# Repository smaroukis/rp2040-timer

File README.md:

# 10k-Hour-Timer-RP2040

An Eval Board for an RP2040 mcu + seven segment LED display + TM1638 driver + peripherals. 

## Project Structure

- `kicad/` - KiCad schematic and PCB design files
- `firmware/` - Firmware source code
- `datasheets/` - Component datasheets and documentation

## Hardware

This project uses the RP2040 microcontroller with supporting circuitry for power management, display drivers, and user interface components.
Note the firmware can be tested using a Raspberry Pi Pico board (original/v1 not Pico 2). 

## Getting Started

TODO - will post build log in the future.

## License

MIT License with other license files attached as used. 

## Hardware Revisions

### 2026-03-22 v1
Tagged commit: <link here>

Thanks to PCBWay for providing a partial discount which I put towards two pre-assemblied. Note that resistors R20 and R22 were populated with 220Ohms instead of 200Ohms as specified in the BOM. However these are just MOFSET gate protection resistors.

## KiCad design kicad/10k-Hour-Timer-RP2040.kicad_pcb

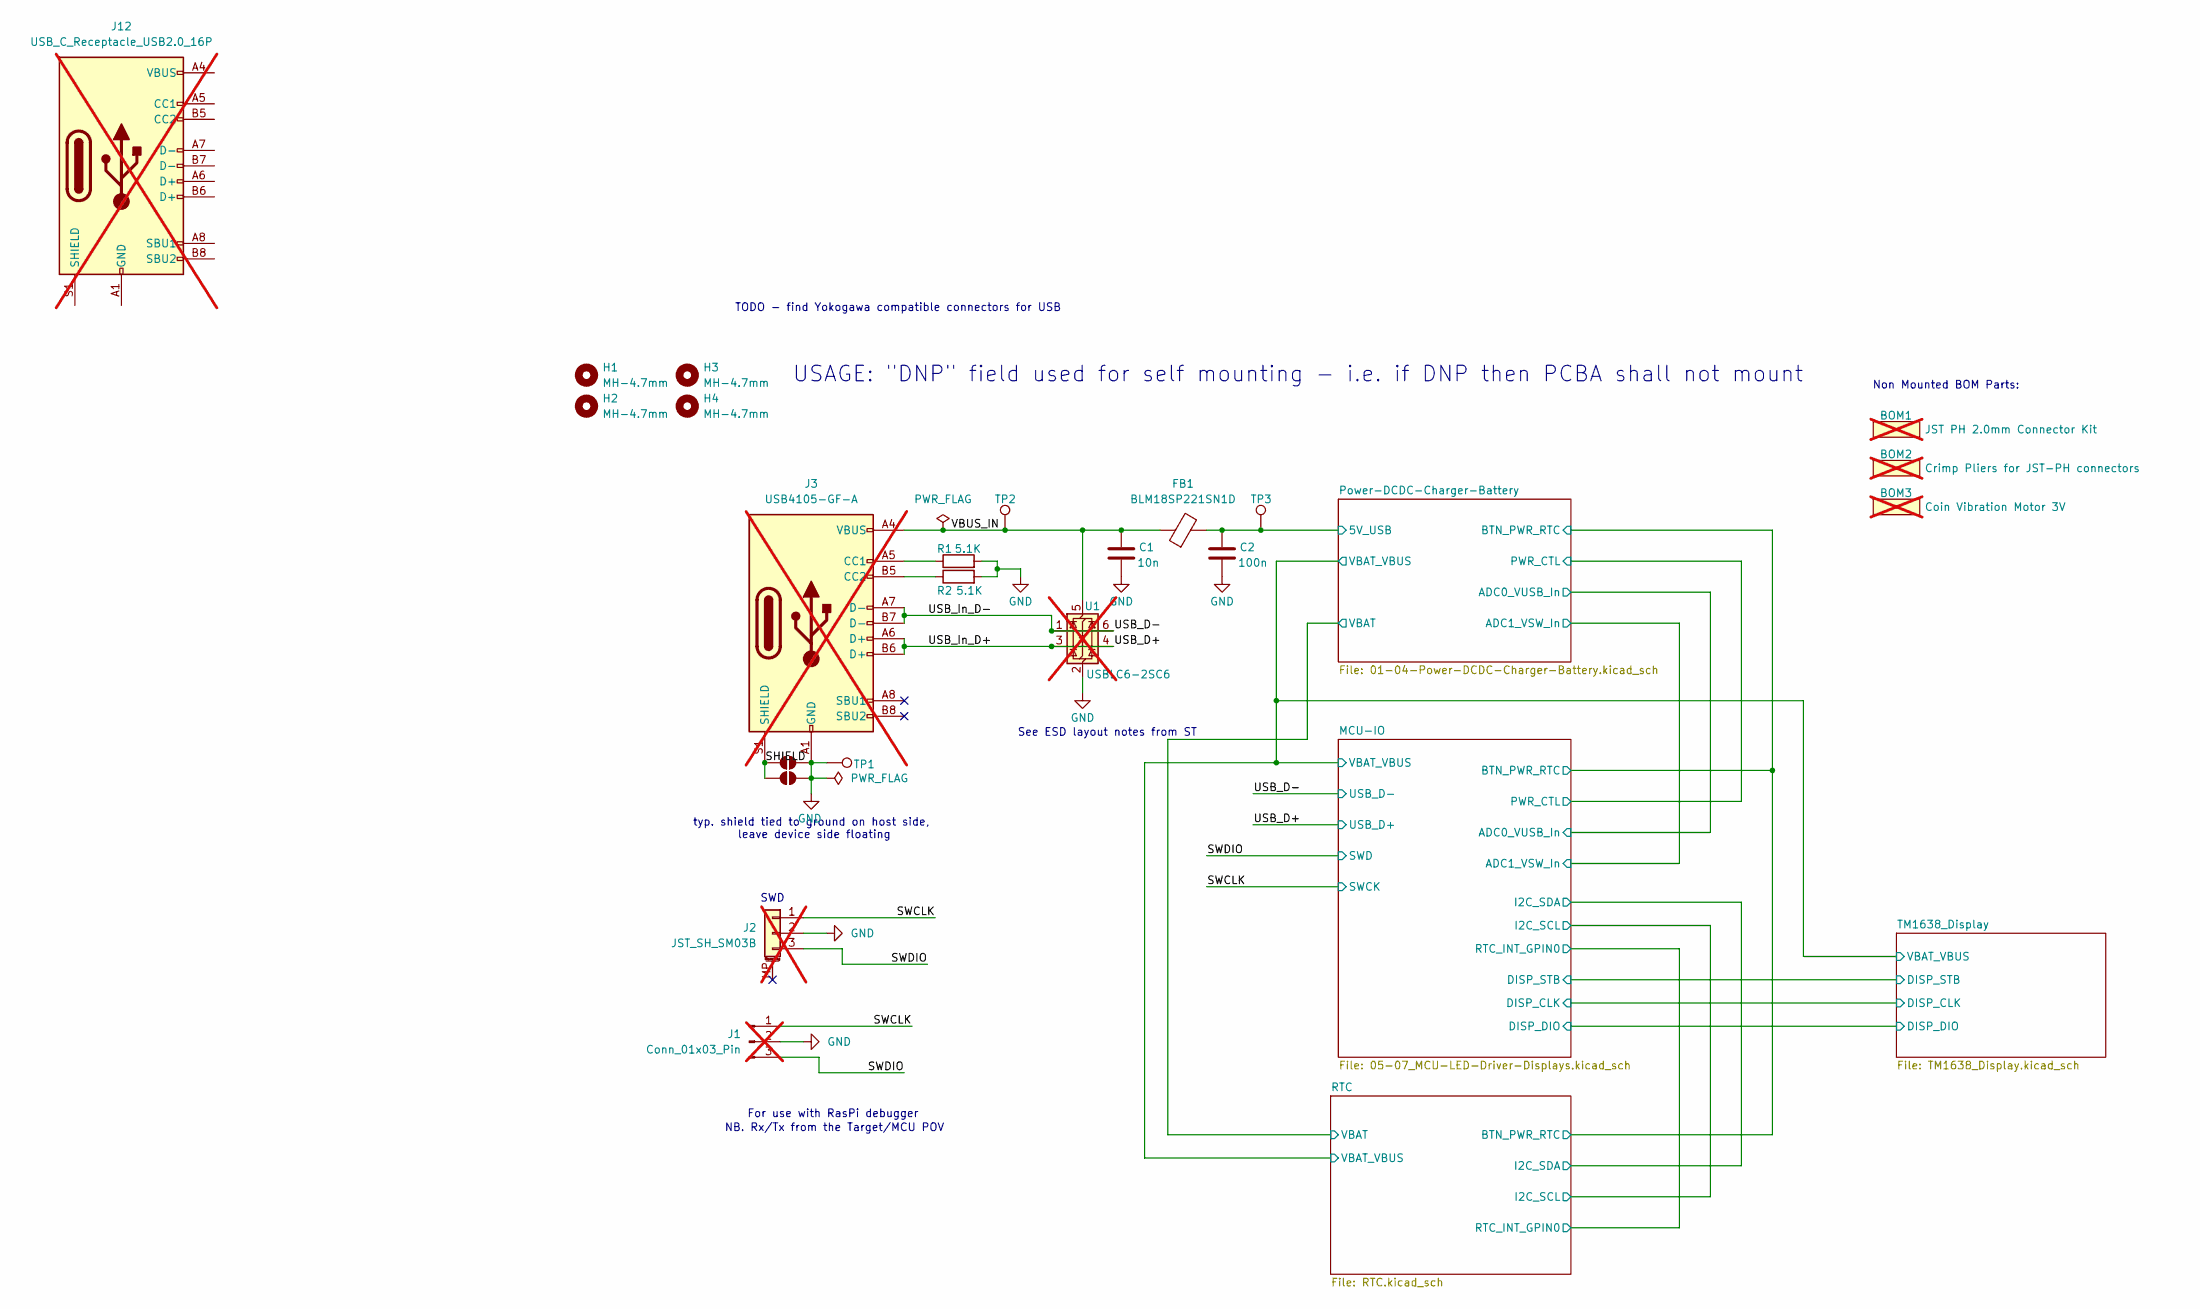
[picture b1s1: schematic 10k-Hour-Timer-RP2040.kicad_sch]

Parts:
BOM1: JST PH 2.0mm Connector Kit; not fitted
BOM2: Crimp Pliers for JST-PH connectors; MPN PA-09; not fitted
BOM3: Coin Vibration Motor 3V; MPN LCM0720A3134F; not fitted
C1: 10n; C_0603_1608Metric_Pad1.08x0.95mm_HandSolder; MPN (Generic)
C2: 100n; C_0603_1608Metric_Pad1.08x0.95mm_HandSolder; MPN (Generic)
FB1: BLM18SP221SN1D; BLM18SP221SN1D_BEADC1608X95N; MPN BLM18SP221SN1D
H1, H2, H3, H4: MH-4.7mm; MountingHole_4.7mm; MPN 8834
J1: Conn_01x03_Pin; PinHeader_1x03_P2.54mm_Vertical; MPN (Embedded); not fitted
J2: JST_SH_SM03B; JST_SH_SM03B-SRSS-TB_1x03-1MP_P1.00mm_Horizontal; MPN SM03B-SRSS-TB(LF)(SN); not fitted
J3: USB4105-GF-A; GCT_USB4105-GF-A; MPN USB4105-GF-A; not fitted
J12: USB_C_Receptacle_USB2.0_16P; USB_C_Receptacle_JAE_DX07S016JA1R1500; MPN DX07S016JA1R1500; not fitted
JP1, JP24: SolderJumper_2_Open; SolderJumper-2_P1.3mm_Open_RoundedPad1.0x1.5mm; MPN (Embedded)
R1, R2: 5.1K; R_0805_2012Metric_Pad1.20x1.40mm_HandSolder; MPN (Generic)
TP1: GND; TestPoint_THTPad_D2.0mm_Drill1.0mm; MPN (Embedded)
TP2: VBUS_IN; TestPoint_THTPad_D2.0mm_Drill1.0mm; MPN (Embedded)
TP3: VBUS; TestPoint_THTPad_D2.0mm_Drill1.0mm; MPN (Embedded)
U1: USBLC6-2SC6; SOT-23-6; MPN USBLC6-2SC6; not fitted

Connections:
/MCU-IO/ADC0_VUSB_In: C2.1, FB1.2, TP3.1; also elsewhere on the board
/SHIELD: J3.S1 (SHIELD), JP1.1 (A), JP24.1 (A)
/SWCLK: J1.1, J2.1; also elsewhere on the board
/SWDIO: J1.3, J2.3; also elsewhere on the board
/USB_D+: J3.A6 (D+), J3.B6 (D+), U1.3 (I/O2), U1.4 (I/O2); also elsewhere on the board
/USB_D-: J3.A7 (D-), J3.B7 (D-), U1.1 (I/O1), U1.6 (I/O1); also elsewhere on the board
/VBUS_IN: C1.1, FB1.1, J3.A4 (VBUS), J3.A9 (VBUS), J3.B4 (VBUS), J3.B9 (VBUS), TP2.1, U1.5 (VBUS)
GND: C1.2, C2.2, J1.2, J2.2, J3.A1 (GND), J3.A12 (GND), J3.B1 (GND), J3.B12 (GND), JP1.2 (B), JP24.2 (B), R1.2, R2.2, TP1.1, U1.2 (GND); also elsewhere on the board
unnamed: J3.A5 (CC1), R1.1
unnamed: J3.B5 (CC2), R2.1
unnamed: J12.A1 (GND), J12.A12 (GND), J12.B1 (GND), J12.B12 (GND)
unnamed: J12.A4 (VBUS), J12.A9 (VBUS), J12.B4 (VBUS), J12.B9 (VBUS)

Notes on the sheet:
For use with RasPi debugger
typ. shield tied to ground on host side, leave device side floating
See ESD layout notes from ST
Non Mounted BOM Parts:
TODO - find Yokogawa compatible connectors for USB
USAGE: "DNP" field used for self mounting - i.e. if DNP then PCBA shall not mount
SWD
NB. Rx/Tx from the Target/MCU POV

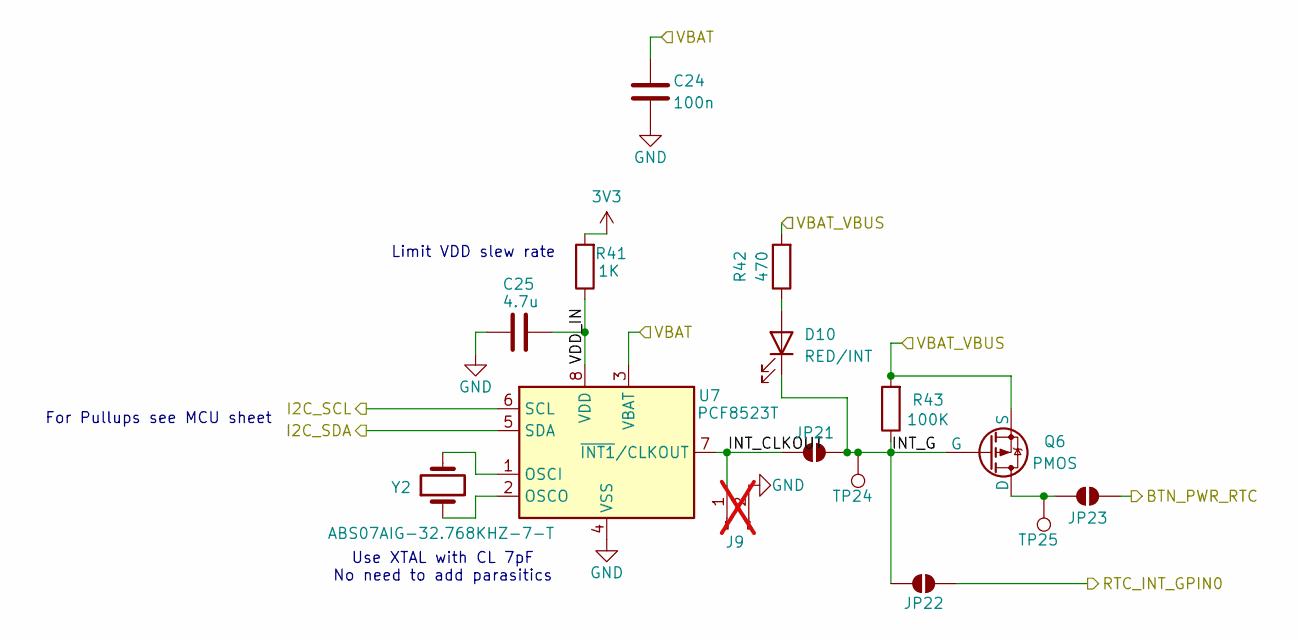
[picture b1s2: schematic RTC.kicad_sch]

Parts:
C24: 100n; C_0603_1608Metric_Pad1.08x0.95mm_HandSolder; MPN (Generic)
C25: 4.7u; C_0603_1608Metric_Pad1.08x0.95mm_HandSolder; MPN (Generic)
D10: RED/INT; LED_0805_2012Metric; MPN NCD0805R1
J9: Conn_01x02_Pin; PinHeader_1x02_P2.54mm_Vertical; not fitted
JP21, JP22, JP23: SolderJumper_2_Open; SolderJumper-2_P1.3mm_Open_RoundedPad1.0x1.5mm; MPN (Embedded)
Q6: PMOS; SOT-23; MPN SI2301CDS-T1-GE3
R41: 1K; R_0805_2012Metric_Pad1.20x1.40mm_HandSolder; MPN (Generic)
R42: 470; R_0805_2012Metric_Pad1.20x1.40mm_HandSolder; MPN (Generic)
R43: 100K; R_0805_2012Metric_Pad1.20x1.40mm_HandSolder; MPN (Generic)
TP24: INT_G; TestPoint_THTPad_D2.0mm_Drill1.0mm; MPN (Embedded)
TP25: INT_D; TestPoint_THTPad_D2.0mm_Drill1.0mm; MPN (Embedded)
U7: PCF8523T; SOIC-8_3.9x4.9mm_P1.27mm; MPN PCF8523T/1,118
Y2: ABS07AIG-32.768KHZ-7-T; Crystal_SMD_3215-2Pin_3.2x1.5mm; MPN ABS07AIG-32.768KHZ-7-T

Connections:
3V3: R41.2; also elsewhere on the board
/MCU-IO/I2C_SCL: U7.6 (SCL); also elsewhere on the board
/MCU-IO/I2C_SDA: U7.5 (SDA); also elsewhere on the board
/MCU-IO/IO_Gate: JP23.2 (B); also elsewhere on the board
/MCU-IO/RTC_INT_GPIN0: JP22.1 (A); also elsewhere on the board
/MCU-IO/VBAT_VBUS: Q6.3 (S), R42.2, R43.2; also elsewhere on the board
/Power-DCDC-Charger-Battery/VBAT: C24.1, U7.3 (VBAT); also elsewhere on the board
/RTC/INT_CLKOUT: J9.1, JP21.1 (A), U7.7 (~INT1/CLKOUT)
/RTC/INT_G: D10.1 (K), JP21.2 (B), JP22.2 (B), Q6.2 (G), R43.1, TP24.1
/RTC/VDD_IN: C25.1, R41.1, U7.8 (VDD)
GND: C24.2, C25.2, J9.2, U7.4 (VSS); also elsewhere on the board
unnamed: D10.2 (A), R42.1
unnamed: JP23.1 (A), Q6.1 (D), TP25.1
unnamed: U7.1 (OSCI), Y2.2
unnamed: U7.2 (OSCO), Y2.1

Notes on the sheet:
For Pullups see MCU sheet
Limit VDD slew rate
Use XTAL with CL 7pF No need to add parasitics

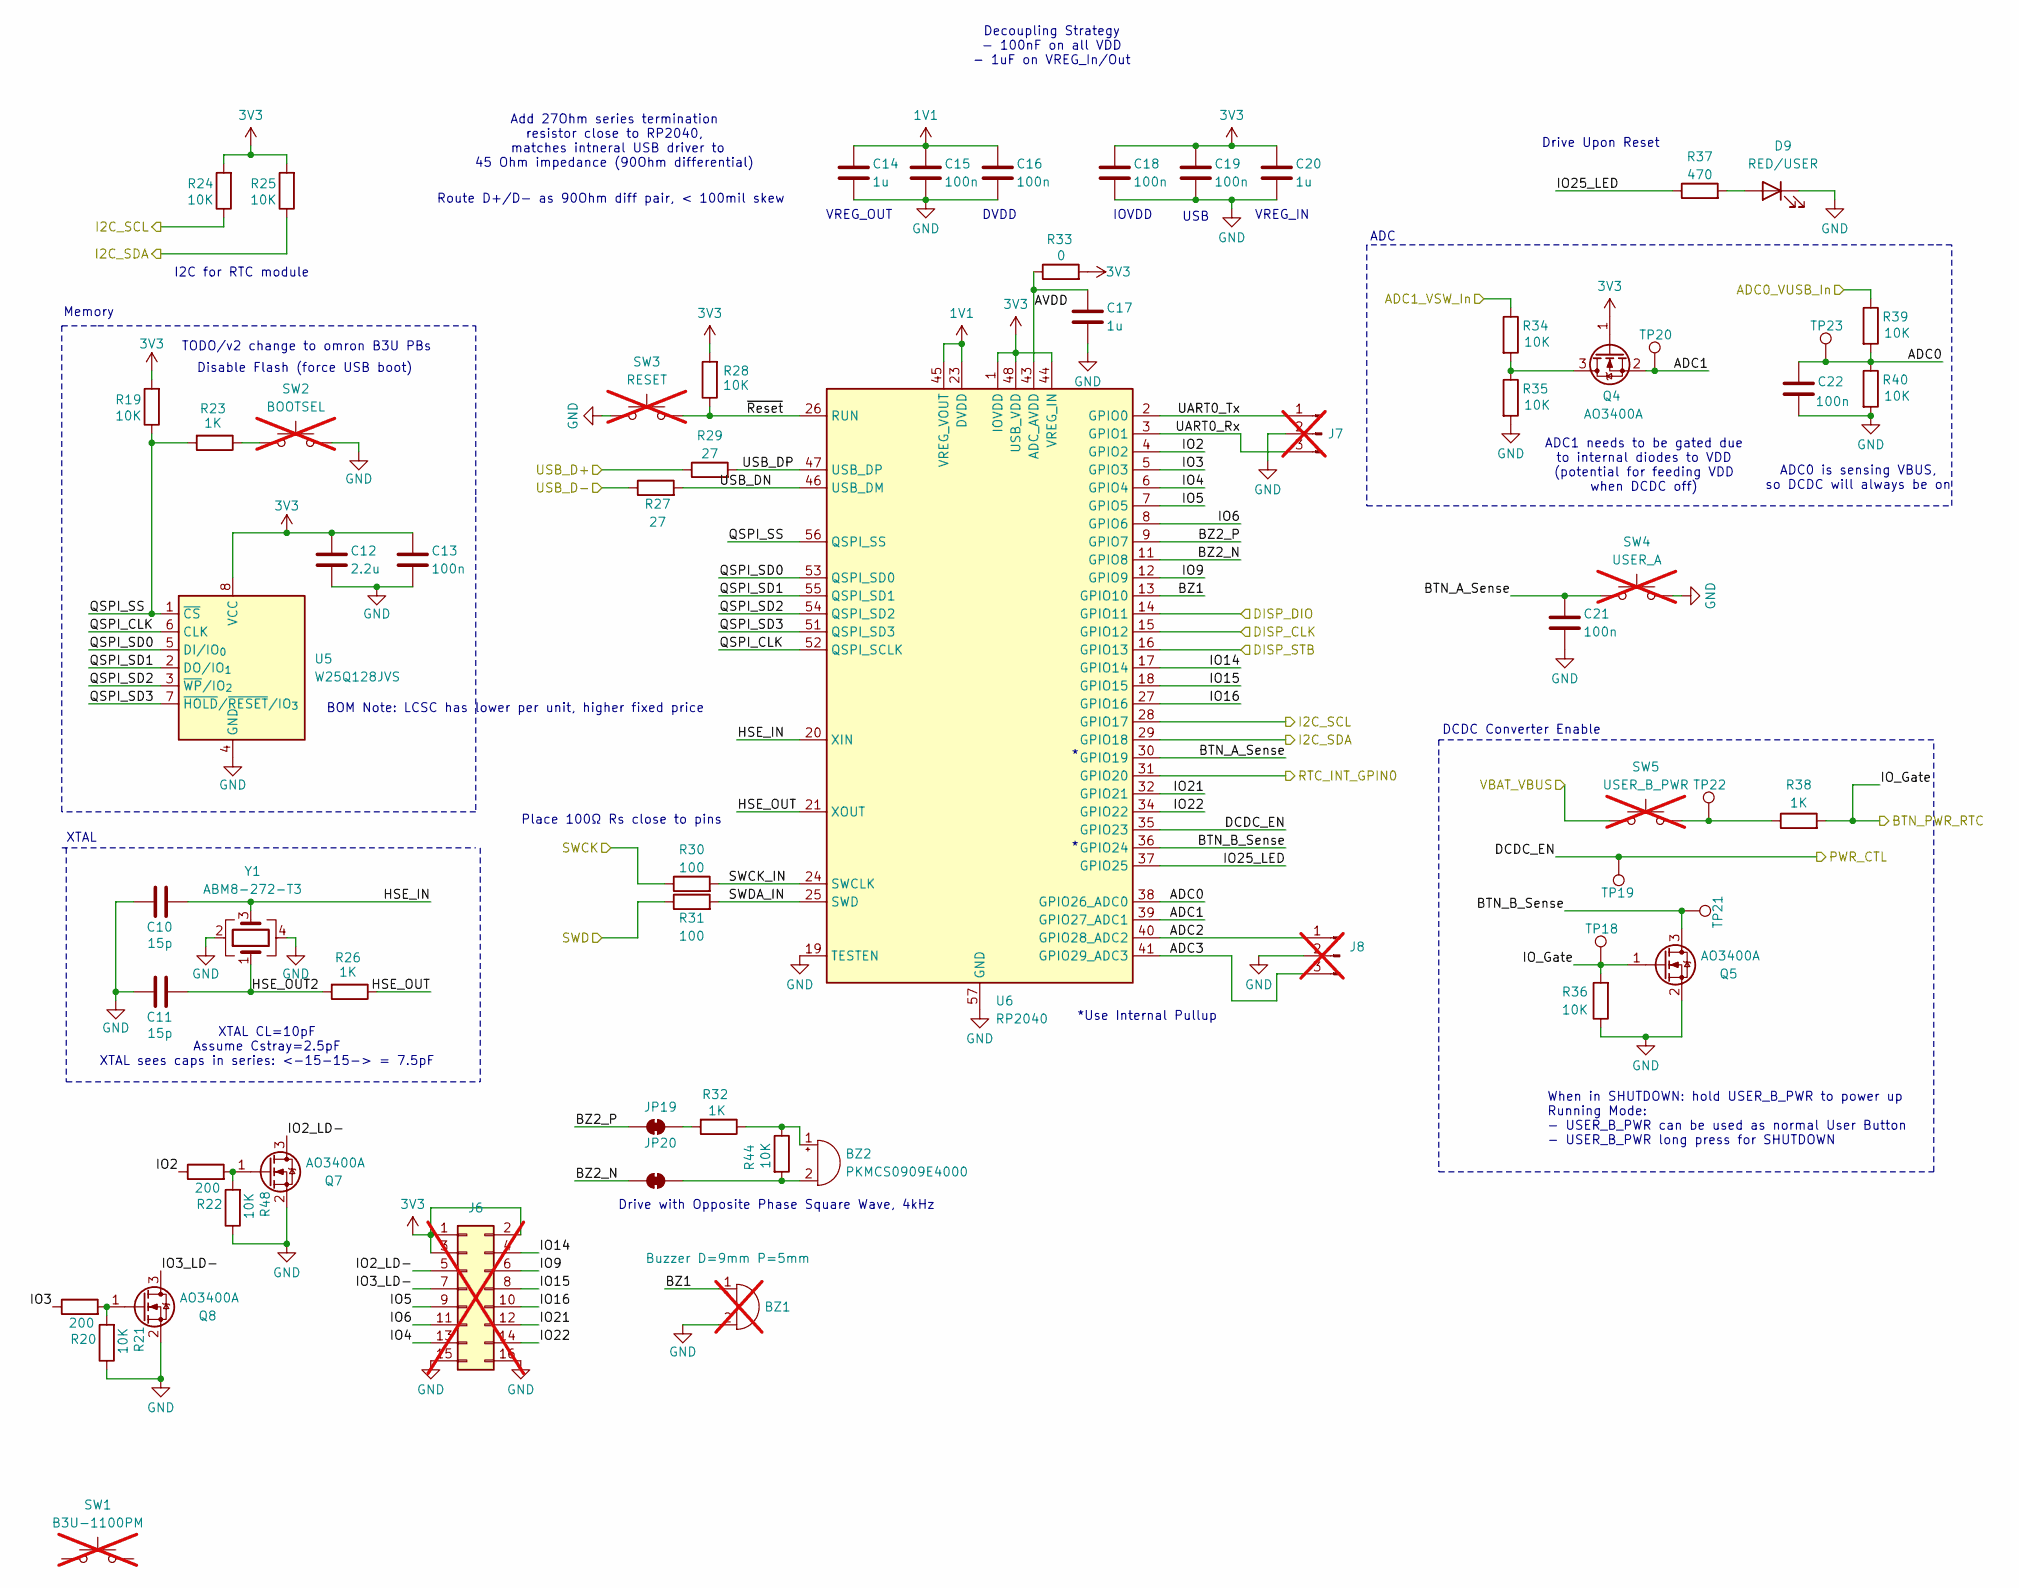
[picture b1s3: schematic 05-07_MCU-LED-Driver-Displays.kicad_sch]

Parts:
BZ1: Buzzer D=9mm P=5mm; Buzzer-TH_D9.6_P5; MPN HNB09A05; not fitted
BZ2: PKMCS0909E4000; Buzzer_SPKR_PKMCS0909E4000-R1; MPN PKMCS0909E4000-R1
C10, C11: 15p; C_0603_1608Metric_Pad1.08x0.95mm_HandSolder; MPN (Generic)
C12: 2.2u; C_0603_1608Metric_Pad1.08x0.95mm_HandSolder; MPN (Generic)
C13, C15, C16, C18, C19, C21, C22: 100n; C_0603_1608Metric_Pad1.08x0.95mm_HandSolder; MPN (Generic)
C14, C17, C20: 1u; C_0603_1608Metric_Pad1.08x0.95mm_HandSolder; MPN (Generic)
D9: RED/USER; LED_0805_2012Metric; MPN NCD0805R1
J6: Conn_02x08_Counter_Clockwise; PinHeader_2x08_P2.54mm_Vertical; not fitted
J7, J8: Conn_01x03_Pin; PinHeader_1x03_P2.54mm_Vertical; MPN (Embedded); not fitted
JP19, JP20: SolderJumper_2_Bridged; SolderJumper-2_P1.3mm_Bridged_RoundedPad1.0x1.5mm; MPN (Embedded)
Q4, Q5, Q7, Q8: AO3400A; SOT-23; MPN AO3400A
R19, R21, R24, R25, R28, R34, R35, R36, R39, R40, R44, R48: 10K; R_0805_2012Metric_Pad1.20x1.40mm_HandSolder; MPN (Generic)
R20, R22: 200; R_0805_2012Metric_Pad1.20x1.40mm_HandSolder; MPN (Generic)
R23, R26, R32, R38: 1K; R_0805_2012Metric_Pad1.20x1.40mm_HandSolder; MPN (Generic)
R27, R29: 27; R_0805_2012Metric_Pad1.20x1.40mm_HandSolder; MPN (Generic)
R30, R31: 100; R_0805_2012Metric_Pad1.20x1.40mm_HandSolder; MPN (Generic)
R33: 0; R_0805_2012Metric_Pad1.20x1.40mm_HandSolder; MPN (Generic)
R37: 470; R_0805_2012Metric_Pad1.20x1.40mm_HandSolder; MPN (Generic)
SW1: B3U-1100PM; SW_SPST_B3U-1100P; MPN B3U-1100PM; not fitted
SW2: BOOTSEL; SW_PUSH_6mm; MPN (Generic)/1825910-6; not fitted
SW3: RESET; SW_PUSH_6mm; MPN (Generic)/1825910-6; not fitted
SW4: USER_A; SW_PUSH_6mm; MPN (Generic)/1825910-6; not fitted
SW5: USER_B_PWR; SW_PUSH_6mm; MPN (Generic)/1825910-6; not fitted
TP18: IOGate; TestPoint_THTPad_D2.0mm_Drill1.0mm; MPN (Embedded)
TP19: DCDC_EN; TestPoint_THTPad_D2.0mm_Drill1.0mm; MPN (Embedded)
TP20: ADC1; TestPoint_THTPad_D2.0mm_Drill1.0mm; MPN (Embedded)
TP21: BTN_B; TestPoint_THTPad_D2.0mm_Drill1.0mm; MPN (Embedded)
TP22: BTN_B_IN; TestPoint_THTPad_D2.0mm_Drill1.0mm; MPN (Embedded)
TP23: ADC0; TestPoint_THTPad_D2.0mm_Drill1.0mm; MPN (Embedded)
U5: W25Q128JVS; SOIC-8_5.3x5.3mm_P1.27mm; MPN W25Q128JVSIQ
U6: RP2040; QFN-56-1EP_7x7mm_P0.4mm_EP3.2x3.2mm; MPN SC0914(13)
Y1: ABM8-272-T3; XTAL_ABM8-272-T3; MPN ABM8-272-T3

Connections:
1V1: C14.1, C15.1, C16.1, U6.23 (DVDD), U6.45 (VREG_VOUT), U6.50 (DVDD)
3V3: C12.1, C13.1, C18.1, C19.1, C20.1, J6.1, J6.2, J6.3, Q4.1 (G), R19.2, R24.2, R25.2, R28.2, R33.2, U5.8 (VCC), U6.1 (IOVDD), U6.10 (IOVDD), U6.22 (IOVDD), U6.33 (IOVDD), U6.42 (IOVDD), U6.44 (VREG_IN), U6.48 (USB_VDD), U6.49 (IOVDD); also elsewhere on the board
/MCU-IO/ADC0: C22.1, R39.2, R40.1, TP23.1, U6.38 (GPIO26_ADC0)
/MCU-IO/ADC0_VUSB_In: R39.1; also elsewhere on the board
/MCU-IO/ADC1: Q4.2 (S), TP20.1, U6.39 (GPIO27_ADC1)
/MCU-IO/ADC1_VSW_In: R34.1; also elsewhere on the board
/MCU-IO/ADC2: J8.1, U6.40 (GPIO28_ADC2)
/MCU-IO/ADC3: J8.3, U6.41 (GPIO29_ADC3)
/MCU-IO/AVDD: C17.1, R33.1, U6.43 (ADC_AVDD)
/MCU-IO/BTN_A_Sense: C21.1, SW4.1, U6.30 (GPIO19)
/MCU-IO/BTN_B_Sense: Q5.3 (D), TP21.1, U6.36 (GPIO24)
/MCU-IO/BZ1: BZ1.1 (+), U6.13 (GPIO10)
/MCU-IO/BZ2_N: JP20.2 (B), U6.11 (GPIO8)
/MCU-IO/BZ2_P: JP19.2 (B), U6.9 (GPIO7)
/MCU-IO/DCDC_EN: TP19.1, U6.35 (GPIO23); also elsewhere on the board
/MCU-IO/DISP_CLK: U6.15 (GPIO12); also elsewhere on the board
/MCU-IO/DISP_DIO: U6.14 (GPIO11); also elsewhere on the board
/MCU-IO/DISP_STB: U6.16 (GPIO13); also elsewhere on the board
/MCU-IO/HSE_IN: C10.2, U6.20 (XIN), Y1.3
/MCU-IO/HSE_OUT: R26.1, U6.21 (XOUT)
/MCU-IO/HSE_OUT2: C11.2, R26.2, Y1.1
/MCU-IO/I2C_SCL: R24.1, U6.28 (GPIO17); also elsewhere on the board
/MCU-IO/I2C_SDA: R25.1, U6.29 (GPIO18); also elsewhere on the board
/MCU-IO/IO2: R22.1, U6.4 (GPIO2)
/MCU-IO/IO2_LD-: J6.5, Q7.3 (D)
/MCU-IO/IO3: R20.1, U6.5 (GPIO3)
/MCU-IO/IO3_LD-: J6.7, Q8.3 (D)
/MCU-IO/IO4: J6.13, U6.6 (GPIO4)
/MCU-IO/IO5: J6.9, U6.7 (GPIO5)
/MCU-IO/IO6: J6.11, U6.8 (GPIO6)
/MCU-IO/IO9: J6.6, U6.12 (GPIO9)
/MCU-IO/IO14: J6.4, U6.17 (GPIO14)
/MCU-IO/IO15: J6.8, U6.18 (GPIO15)
/MCU-IO/IO16: J6.10, U6.27 (GPIO16)
/MCU-IO/IO21: J6.12, U6.32 (GPIO21)
/MCU-IO/IO22: J6.14, U6.34 (GPIO22)
/MCU-IO/IO25_LED: R37.1, U6.37 (GPIO25)
/MCU-IO/IO_Gate: Q5.1 (G), R36.2, R38.2, TP18.1; also elsewhere on the board
/MCU-IO/QSPI_CLK: U5.6 (CLK), U6.52 (QSPI_SCLK)
/MCU-IO/QSPI_SD0: U5.5 (DI/IO_{0}), U6.53 (QSPI_SD0)
/MCU-IO/QSPI_SD1: U5.2 (DO/IO_{1}), U6.55 (QSPI_SD1)
/MCU-IO/QSPI_SD2: U5.3 (~WP/IO_{2}), U6.54 (QSPI_SD2)
/MCU-IO/QSPI_SD3: U5.7 (~HOLD/~RESET/IO_{3}), U6.51 (QSPI_SD3)
/MCU-IO/QSPI_SS: R19.1, R23.2, U5.1 (~CS), U6.56 (QSPI_SS)
/MCU-IO/RTC_INT_GPIN0: U6.31 (GPIO20); also elsewhere on the board
/MCU-IO/SWCK_IN: R30.2, U6.24 (SWCLK)
/MCU-IO/SWDA_IN: R31.2, U6.25 (SWD)
/MCU-IO/UART0_Rx: J7.3, U6.3 (GPIO1)
/MCU-IO/UART0_Tx: J7.1, U6.2 (GPIO0)
/MCU-IO/USB_DN: R27.2, U6.46 (USB_DM)
/MCU-IO/USB_DP: R29.2, U6.47 (USB_DP)
/MCU-IO/VBAT_VBUS: SW5.1; also elsewhere on the board
/MCU-IO/~Reset: R28.1, SW3.2, U6.26 (RUN)
/SWCLK: R30.1; also elsewhere on the board
/SWDIO: R31.1; also elsewhere on the board
/USB_D+: R29.1; also elsewhere on the board
/USB_D-: R27.1; also elsewhere on the board
GND: BZ1.2 (-), C10.1, C11.1, C12.2, C13.2, C14.2, C15.2, C16.2, C17.2, C18.2, C19.2, C20.2, C21.2, C22.2, D9.1 (K), J6.15, J6.16, J7.2, J8.2, Q5.2 (S), Q7.2 (S), Q8.2 (S), R21.1, R35.2, R36.1, R40.2, R48.1, SW2.2, SW3.1, SW4.2, U5.4 (GND), U6.19 (TESTEN), U6.57 (GND), Y1.2, Y1.4; also elsewhere on the board
unnamed: BZ2.1 (+), R32.1, R44.1
unnamed: BZ2.2 (-), JP20.1 (A), R44.2
unnamed: D9.2 (A), R37.2
unnamed: JP19.1 (A), R32.2
unnamed: Q4.3 (D), R34.2, R35.1
unnamed: Q7.1 (G), R22.2, R48.2
unnamed: Q8.1 (G), R20.2, R21.2
unnamed: R23.1, SW2.1
unnamed: R38.1, SW5.2, TP22.1

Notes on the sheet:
Route D+/D- as 90Ohm diff pair, < 100mil skew
XTAL
TODO/v2 change to omron B3U PBs
XTAL CL=10pF Assume Cstray=2.5pF XTAL sees caps in series: <-15-15-> = 7.5pF
Disable Flash (force USB boot)
BOM Note: LCSC has lower per unit, higher fixed price
When in SHUTDOWN: hold USER_B_PWR to power up Running Mode: - USER_B_PWR can be used as normal User Button - USER_B_PWR long press for SHUTDOWN
I2C for RTC module
IOVDD
ADC0 is sensing VBUS, so DCDC will always be on
VREG_OUT
USB
Add 27Ohm series termination resistor close to RP2040, matches intneral USB driver to 45 Ohm impedance (90Ohm differential)
*Use Internal Pullup
Place 100Ω Rs close to pins
DCDC Converter Enable
Memory
Drive Upon Reset
Decoupling Strategy - 100nF on all VDD - 1uF on VREG_In/Out
Drive with Opposite Phase Square Wave, 4kHz
ADC
VREG_IN
DVDD
ADC1 needs to be gated due to internal diodes to VDD (potential for feeding VDD when DCDC off)

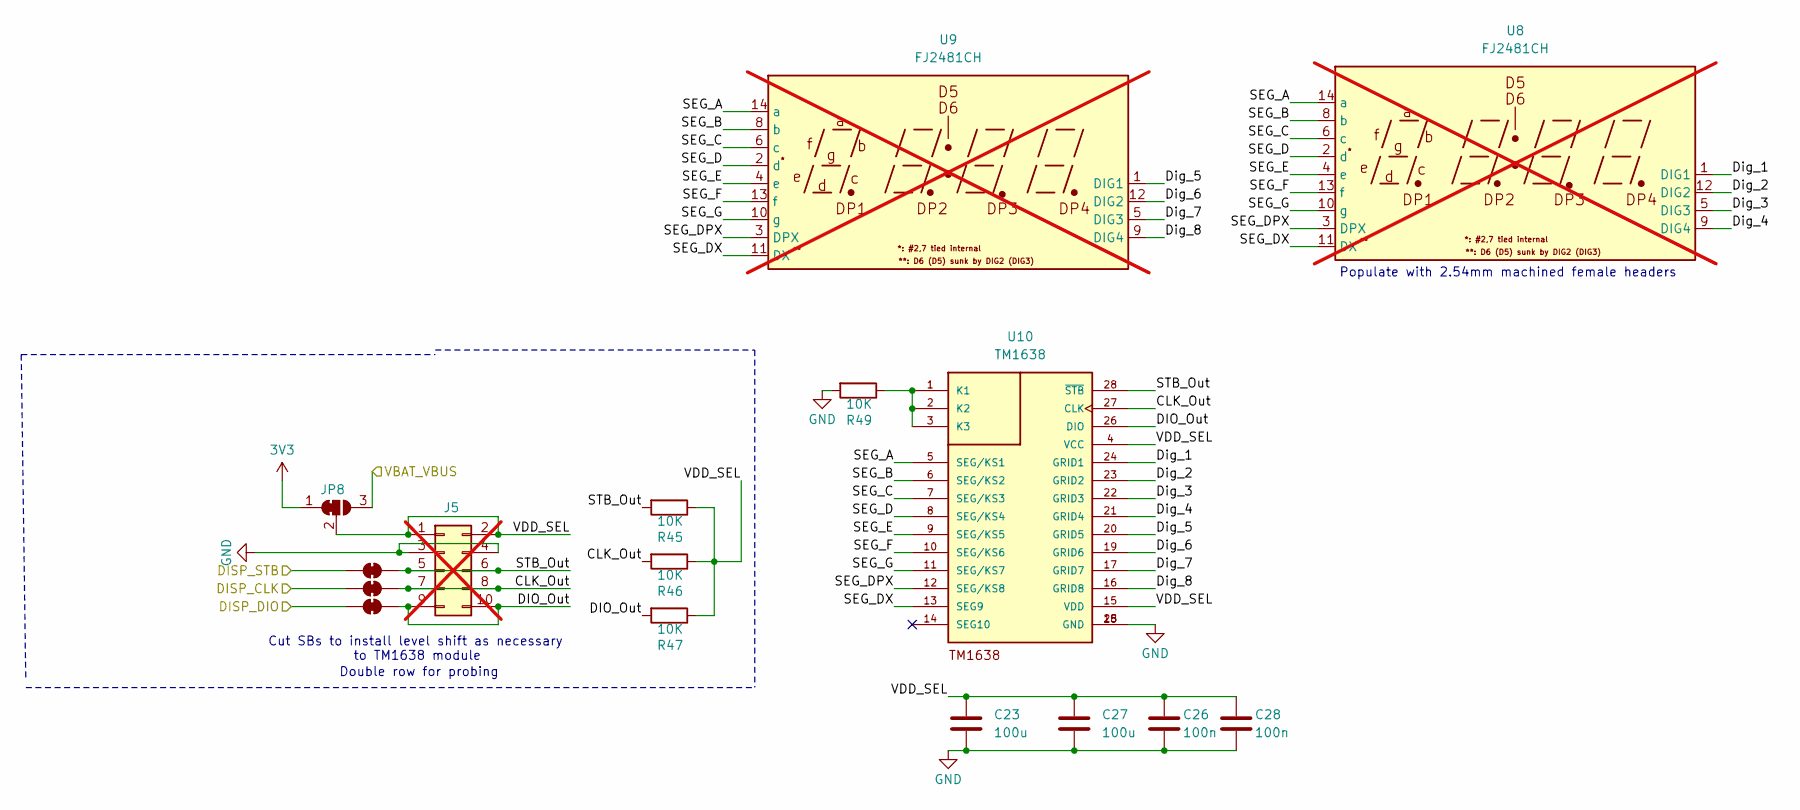
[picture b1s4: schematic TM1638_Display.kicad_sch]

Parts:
C23, C27: 100u; C_1206_3216Metric; MPN CL31A107MQHNNNE
C26, C28: 100n; C_0603_1608Metric_Pad1.08x0.95mm_HandSolder; MPN (Generic)
J5: Conn_02x05_Counter_Clockwise; PinHeader_2x05_P2.54mm_Vertical; not fitted
JP8: SolderJumper_3_Bridged12; SolderJumper-3_P1.3mm_Bridged12_RoundedPad1.0x1.5mm
JP16, JP17, JP18: SolderJumper_2_Bridged; SolderJumper-2_P1.3mm_Bridged_RoundedPad1.0x1.5mm; MPN (Embedded)
R45, R46, R47, R49: 10K; R_0805_2012Metric_Pad1.20x1.40mm_HandSolder; MPN (Generic)
U8, U9: FJ2481CH; 7-Seg-CC28-FJ2481CH; MPN FJ2481CH; not fitted
U10: TM1638; SOIC127P1041X265-28N; MPN TM1638

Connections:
3V3: JP8.1 (A); also elsewhere on the board
/MCU-IO/DISP_CLK: JP17.2 (B); also elsewhere on the board
/MCU-IO/DISP_DIO: JP18.2 (B); also elsewhere on the board
/MCU-IO/DISP_STB: JP16.2 (B); also elsewhere on the board
/MCU-IO/VBAT_VBUS: JP8.3 (B); also elsewhere on the board
/TM1638_Display/CLK_Out: J5.7, J5.8, JP17.1 (A), R46.2, U10.27 (CLK)
/TM1638_Display/DIO_Out: J5.9, J5.10, JP18.1 (A), R47.2, U10.26 (DIO)
/TM1638_Display/Dig_1: U8.1 (DIG1), U10.24 (GRID1)
/TM1638_Display/Dig_2: U8.12 (DIG2), U10.23 (GRID2)
/TM1638_Display/Dig_3: U8.5 (DIG3), U10.22 (GRID3)
/TM1638_Display/Dig_4: U8.9 (DIG4), U10.21 (GRID4)
/TM1638_Display/Dig_5: U9.1 (DIG1), U10.20 (GRID5)
/TM1638_Display/Dig_6: U9.12 (DIG2), U10.19 (GRID6)
/TM1638_Display/Dig_7: U9.5 (DIG3), U10.17 (GRID7)
/TM1638_Display/Dig_8: U9.9 (DIG4), U10.16 (GRID8)
/TM1638_Display/SEG_A: U8.14 (a), U9.14 (a), U10.5 (SEG/KS1)
/TM1638_Display/SEG_B: U8.8 (b), U9.8 (b), U10.6 (SEG/KS2)
/TM1638_Display/SEG_C: U8.6 (c), U9.6 (c), U10.7 (SEG/KS3)
/TM1638_Display/SEG_D: U8.2 (d), U8.7 (NA), U9.2 (d), U9.7 (NA), U10.8 (SEG/KS4)
/TM1638_Display/SEG_DPX: U8.3 (DPX), U9.3 (DPX), U10.12 (SEG/KS8)
/TM1638_Display/SEG_DX: U8.11 (DX), U9.11 (DX), U10.13 (SEG9)
/TM1638_Display/SEG_E: U8.4 (e), U9.4 (e), U10.9 (SEG/KS5)
/TM1638_Display/SEG_F: U8.13 (f), U9.13 (f), U10.10 (SEG/KS6)
/TM1638_Display/SEG_G: U8.10 (g), U9.10 (g), U10.11 (SEG/KS7)
/TM1638_Display/STB_Out: J5.5, J5.6, JP16.1 (A), R45.2, U10.28 (~STB)
/TM1638_Display/VDD_SEL: C23.1, C26.1, C27.1, C28.1, J5.1, J5.2, JP8.2 (C), R45.1, R46.1, R47.1, U10.4 (VCC), U10.15 (VDD)
GND: C23.2, C26.2, C27.2, C28.2, J5.3, J5.4, R49.2, U10.18 (GND), U10.25 (GND); also elsewhere on the board
unnamed: R49.1, U10.1 (K1), U10.2 (K2), U10.3 (K3)

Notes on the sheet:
to TM1638 module
Populate with 2.54mm machined female headers
Double row for probing
Cut SBs to install level shift as necessary

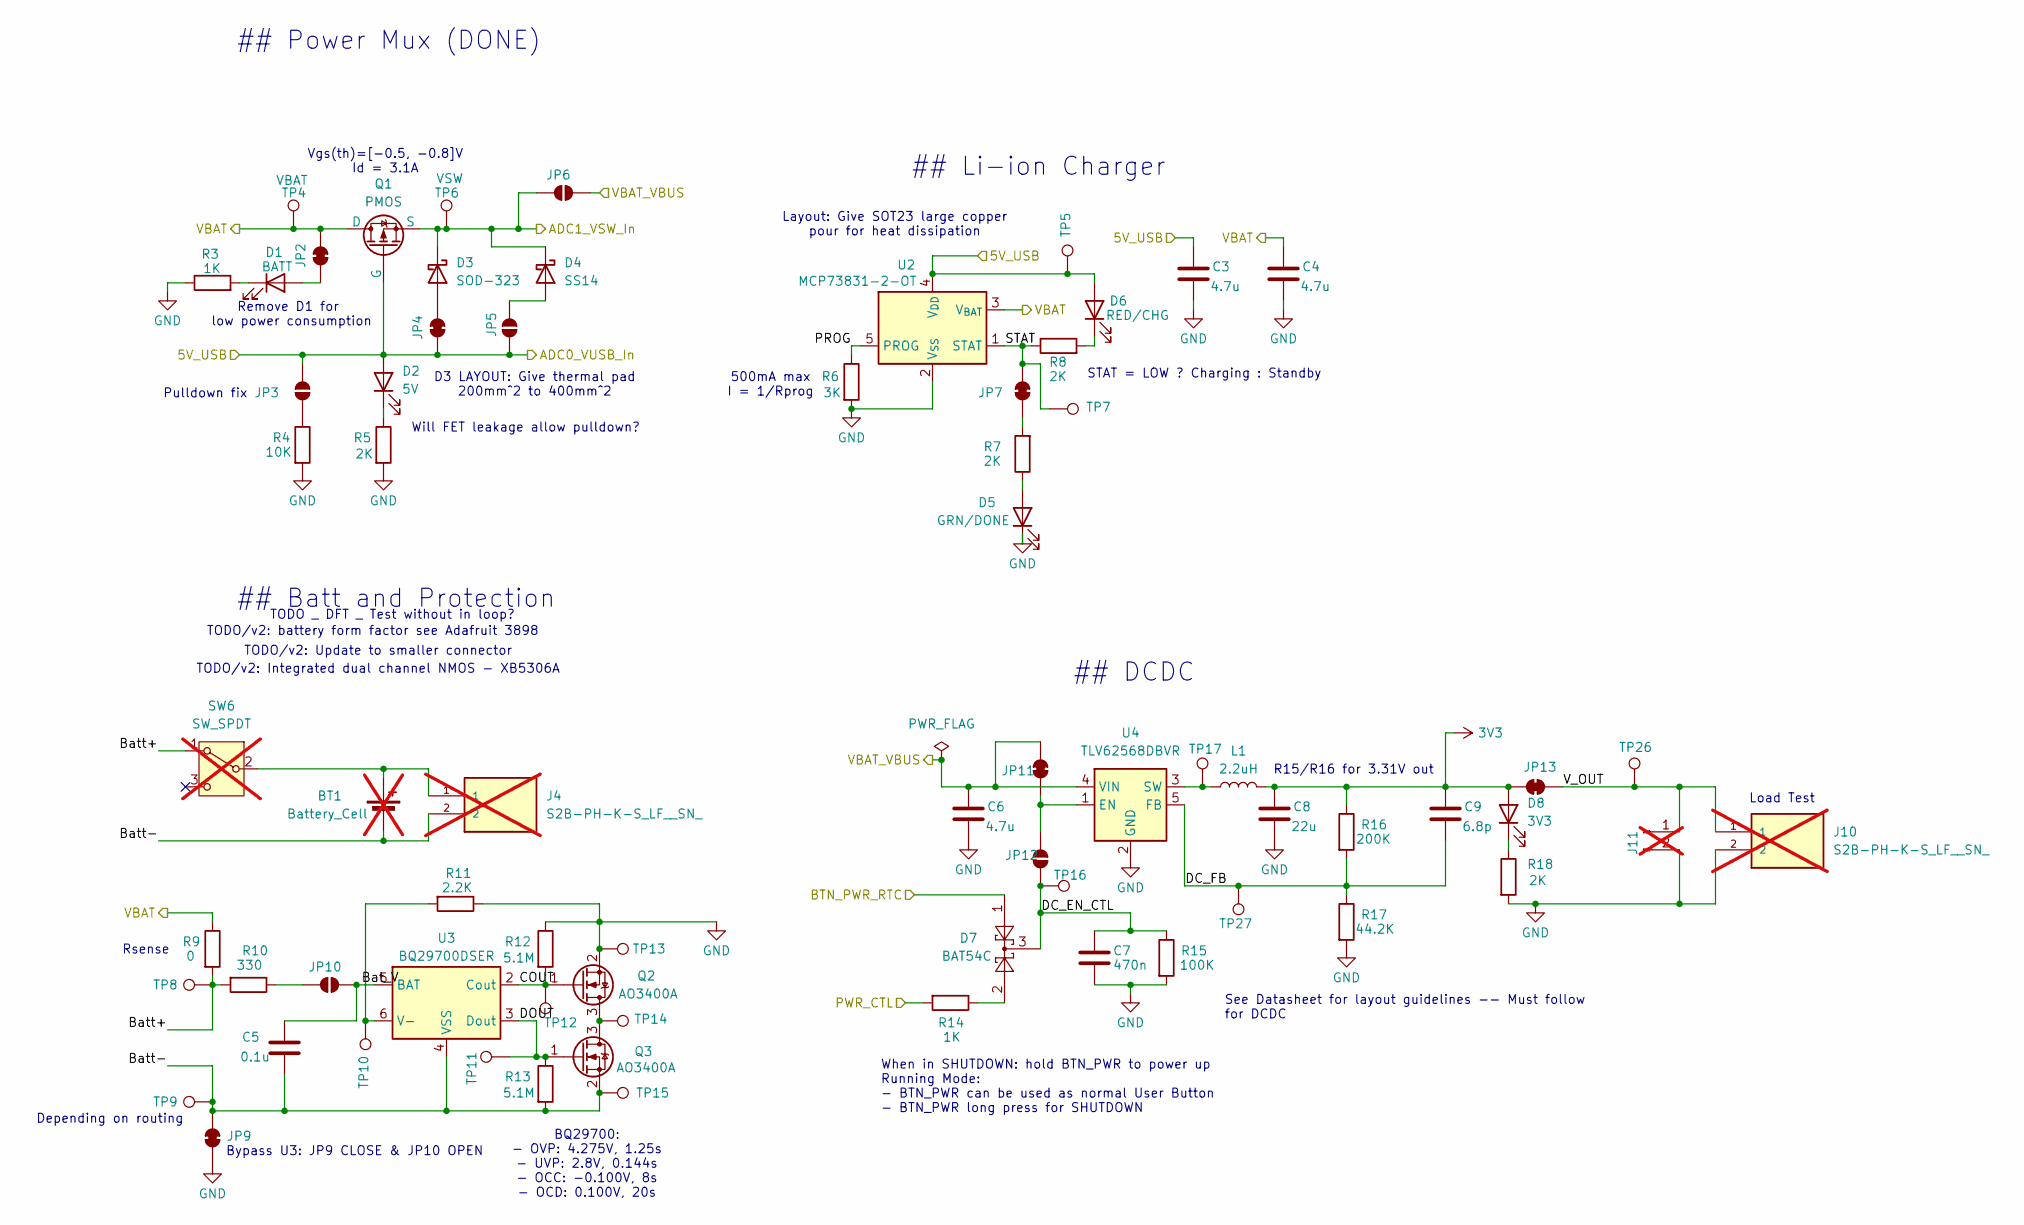
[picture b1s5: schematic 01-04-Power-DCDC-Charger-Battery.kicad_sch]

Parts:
BT1: Battery_Cell; Battery-Holder-BH-123A_37.5P_1.8D_MH; MPN BH-123A-A1CJ002; not fitted
C3, C4, C6: 4.7u; C_0603_1608Metric_Pad1.08x0.95mm_HandSolder; MPN (Generic)
C5: 0.1u; C_0603_1608Metric_Pad1.08x0.95mm_HandSolder; MPN (Generic)
C7: 470n; C_0603_1608Metric_Pad1.08x0.95mm_HandSolder; MPN (Generic)
C8: 22u; C_0603_1608Metric_Pad1.08x0.95mm_HandSolder; MPN CL10A226MQ8NRNC
C9: 6.8p; C_0603_1608Metric_Pad1.08x0.95mm_HandSolder; MPN (Generic)
D1: BATT; LED_0805_2012Metric; MPN KT-0805G
D2: 5V; LED_0805_2012Metric; MPN KT-0805G
D3: SOD-323; D_SOD-323_HandSoldering; MPN PMEG1020EA,115
D4: SS14; D_SMA; MPN SS14 (Generic)
D5: GRN/DONE; LED_0805_2012Metric; MPN KT-0805G
D6: RED/CHG; LED_0805_2012Metric; MPN NCD0805R1
D7: BAT54C; SOT-23; MPN BAT54CLT1G
D8: 3V3; LED_0805_2012Metric; MPN KT-0805G
J4, J10: S2B-PH-K-S_LF__SN_; JST_PH_S2B-PH-K_1x02_P2.00mm_Horizontal; MPN S2B-PH-K-S; not fitted
J11: Conn_01x02_Pin; PinHeader_1x02_P2.54mm_Vertical; not fitted
JP2, JP4, JP7, JP9, JP11, JP13: SolderJumper_2_Bridged; SolderJumper-2_P1.3mm_Bridged_RoundedPad1.0x1.5mm; MPN (Embedded)
JP3, JP5, JP6, JP10, JP12: SolderJumper_2_Open; SolderJumper-2_P1.3mm_Open_RoundedPad1.0x1.5mm; MPN (Embedded)
L1: 2.2uH; IND_SDER041H-2R2MS; MPN SDER041H-2R2MS
Q1: PMOS; SOT-23; MPN SI2301CDS-T1-GE3
Q2, Q3: AO3400A; SOT-23; MPN AO3400A
R3, R14: 1K; R_0805_2012Metric_Pad1.20x1.40mm_HandSolder; MPN (Generic)
R4: 10K; R_0805_2012Metric_Pad1.20x1.40mm_HandSolder; MPN (Generic)
R5, R7, R8, R18: 2K; R_0805_2012Metric_Pad1.20x1.40mm_HandSolder; MPN (Generic)
R6: 3K; R_0805_2012Metric_Pad1.20x1.40mm_HandSolder; MPN (Generic)
R9: 0; R_0805_2012Metric_Pad1.20x1.40mm_HandSolder; MPN (Generic)
R10: 330; R_0805_2012Metric_Pad1.20x1.40mm_HandSolder; MPN (Generic)
R11: 2.2K; R_0805_2012Metric_Pad1.20x1.40mm_HandSolder; MPN (Generic)
R12, R13: 5.1M; R_0805_2012Metric_Pad1.20x1.40mm_HandSolder; MPN (Generic)
R15: 100K; R_0805_2012Metric_Pad1.20x1.40mm_HandSolder; MPN (Generic)
R16: 200K; R_0805_2012Metric_Pad1.20x1.40mm_HandSolder; MPN (Generic)
R17: 44.2K; R_0805_2012Metric_Pad1.20x1.40mm_HandSolder; MPN (Generic)
SW6: SW_SPDT; SW_E-Switch_EG1271_SPDT; MPN EG1271; not fitted
TP4: VBAT; TestPoint_THTPad_D2.0mm_Drill1.0mm; MPN (Embedded)
TP5: U2_VDD; TestPoint_THTPad_D2.0mm_Drill1.0mm; MPN (Embedded)
TP6: VSW; TestPoint_THTPad_D2.0mm_Drill1.0mm; MPN (Embedded)
TP7: STAT; TestPoint_THTPad_D2.0mm_Drill1.0mm; MPN (Embedded)
TP8: BAT+; TestPoint_THTPad_D2.0mm_Drill1.0mm; MPN (Embedded)
TP9, TP15: BAT-; TestPoint_THTPad_D2.0mm_Drill1.0mm; MPN (Embedded)
TP10: U3_V-; TestPoint_THTPad_D2.0mm_Drill1.0mm; MPN (Embedded)
TP11: DSG; TestPoint_THTPad_D2.0mm_Drill1.0mm; MPN (Embedded)
TP12: CHG; TestPoint_THTPad_D2.0mm_Drill1.0mm; MPN (Embedded)
TP13: GND; TestPoint_THTPad_D2.0mm_Drill1.0mm; MPN (Embedded)
TP14: Q23_D; TestPoint_THTPad_D2.0mm_Drill1.0mm; MPN (Embedded)
TP16: EN_CTL; TestPoint_THTPad_D2.0mm_Drill1.0mm; MPN (Embedded)
TP17: DC_SW; TestPoint_THTPad_D2.0mm_Drill1.0mm; MPN (Embedded)
TP26: LOAD; TestPoint_THTPad_D2.0mm_Drill1.0mm; MPN (Embedded)
TP27: FB; TestPoint_THTPad_D2.0mm_Drill1.0mm; MPN (Embedded)
U2: MCP73831-2-OT; SOT-23-5; MPN MCP73831T-2ACI/OT
U3: BQ29700DSER; WSON-6_1.5x1.5mm_P0.5mm; MPN BQ29700DSER
U4: TLV62568DBVR; SOT-23-5; MPN TLV62568DBVR

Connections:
3V3: C8.1, C9.1, D8.2 (A), JP13.2 (B), L1.2, R16.1; also elsewhere on the board
/MCU-IO/ADC0_VUSB_In: C3.1, D2.2 (A), D6.2 (A), JP3.2 (B), JP4.2 (B), JP5.1 (A), Q1.2 (G), TP5.1, U2.4 (V_{DD}); also elsewhere on the board
/MCU-IO/ADC1_VSW_In: D3.1 (K), D4.1 (K), JP6.2 (B), Q1.3 (S), TP6.1; also elsewhere on the board
/MCU-IO/DCDC_EN: R14.2; also elsewhere on the board
/MCU-IO/IO_Gate: D7.1; also elsewhere on the board
/MCU-IO/VBAT_VBUS: C6.1, JP6.1 (A), JP11.2 (B), U4.4 (VIN); also elsewhere on the board
/Power-DCDC-Charger-Battery/Bat_V: C5.1, JP10.1 (A), U3.5 (BAT)
/Power-DCDC-Charger-Battery/Batt+: R9.2, R10.2, SW6.1 (A), TP8.1
/Power-DCDC-Charger-Battery/Batt-: BT1.2 (-), C5.2, J4.2, JP9.1 (A), Q3.2 (S), R13.2, TP9.1, TP15.1, U3.4 (VSS)
/Power-DCDC-Charger-Battery/COUT: Q2.1 (G), R12.2, TP12.1, U3.2 (Cout)
/Power-DCDC-Charger-Battery/DC_EN_CTL: C7.1, D7.3, JP12.1 (A), R15.1, TP16.1
/Power-DCDC-Charger-Battery/DC_FB: C9.2, R16.2, R17.1, TP27.1, U4.5 (FB)
/Power-DCDC-Charger-Battery/DOUT: Q3.1 (G), R13.1, TP11.1, U3.3 (Dout)
/Power-DCDC-Charger-Battery/PROG: R6.1, U2.5 (PROG)
/Power-DCDC-Charger-Battery/STAT: JP7.2 (B), R8.1, TP7.1, U2.1 (STAT)
/Power-DCDC-Charger-Battery/VBAT: C4.1, JP2.1 (A), Q1.1 (D), R9.1, TP4.1, U2.3 (V_{BAT}); also elsewhere on the board
/Power-DCDC-Charger-Battery/V_OUT: J10.1, J11.1, JP13.1 (A), TP26.1
GND: C3.2, C4.2, C6.2, C7.2, C8.2, D5.1 (K), J10.2, J11.2, JP9.2 (B), Q2.2 (S), R3.1, R4.2, R5.2, R6.2, R11.1, R12.1, R15.2, R17.2, R18.2, TP13.1, U2.2 (V_{SS}), U4.2 (GND); also elsewhere on the board
unnamed: BT1.1 (+), J4.1, SW6.2 (B)
unnamed: D1.2 (A), JP2.2 (B)
unnamed: D1.1 (K), R3.2
unnamed: D2.1 (K), R5.1
unnamed: D3.2 (A), JP4.1 (A)
unnamed: D4.2 (A), JP5.2 (B)
unnamed: D5.2 (A), R7.1
unnamed: D6.1 (K), R8.2
unnamed: D7.2, R14.1
unnamed: D8.1 (K), R18.1
unnamed: JP3.1 (A), R4.1
unnamed: JP7.1 (A), R7.2
unnamed: JP10.2 (B), R10.1
unnamed: JP11.1 (A), JP12.2 (B), U4.1 (EN)
unnamed: Q2.3 (D), Q3.3 (D), TP14.1
unnamed: R11.2, TP10.1, U3.6 (V-)
unnamed: L1.1, TP17.1, U4.3 (SW)

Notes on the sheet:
Depending on routing
## DCDC
BQ29700: - OVP: 4.275V, 1.25s - UVP: 2.8V, 0.144s - OCC: -0.100V, 8s - OCD: 0.100V, 20s
D3 LAYOUT: Give thermal pad 200mm^2 to 400mm^2
TODO/v2: Update to smaller connector
Layout: Give SOT23 large copper pour for heat dissipation
R15/R16 for 3.31V out
Load Test
Pulldown fix
Vgs(th)=[-0.5, -0.8]V Id = 3.1A
When in SHUTDOWN: hold BTN_PWR to power up Running Mode: - BTN_PWR can be used as normal User Button - BTN_PWR long press for SHUTDOWN
TODO _ DFT _ Test without in loop?
See Datasheet for layout guidelines -- Must follow for DCDC
STAT = LOW ? Charging : Standby
TODO/v2: battery form factor see Adafruit 3898
Bypass U3: JP9 CLOSE & JP10 OPEN
## Power Mux (DONE)
## Li-ion Charger
Remove D1 for low power consumption
Will FET leakage allow pulldown?
TODO/v2: Integrated dual channel NMOS - XB5306A
## Batt and Protection
500mA max I = 1/Rprog
Rsense
